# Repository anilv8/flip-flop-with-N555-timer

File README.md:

# Flip-Flop Circuit with N555 Timer
Double Sided PCB design of Flip-Flop circuitwith NE555 Timer using KiCad.
Dimensions: 25 mm x 27 mm.

# Schematic of circuit

### ERC Result:

# PCB Board
### Front Copper:

### Back Copper:

### Silkscreen:

## DRC Result:

## 3D view of PCB
### Front:

### Back:

# Gerber
### Front Copper:

### Back Copper:

# BOM
| Id  | Designator | Footprint | Quantity | Designation | Supplier and ref |
| --- | --- | --- | --- | --- | --- |
| 1   | R3  | R_Axial_DIN0204_L3.6mm_D1.6mm_P5.08mm_Horizontal | 1   | 100k |     |
| 2   | R4  | R_Axial_DIN0204_L3.6mm_D1.6mm_P5.08mm_Horizontal | 1   | 50k |     |
| 3   | D1,D2 | LED_D3.0mm | 2   | LED |     |
| 4   | U1  | DIP-8_W7.62mm_LongPads | 1   | NE555P |     |
| 5   | R2,R1 | R_Axial_DIN0204_L3.6mm_D1.6mm_P5.08mm_Horizontal | 2   | 330 |     |
| 6   | C2  | CP_Radial_D6.3mm_P2.50mm | 1   | 10u |     |
| 7   | C3  | C_Disc_D3.0mm_W1.6mm_P2.50mm | 1   | 0.1u |     |
| 8   | J2  | Molex_KK-254_AE-6410-02A_1x02\P2.54mm_Vertical | 1   | Conn\_01x02\_Pin |     |

# REFERENCES
[1]  https://www.udemy.com/course/kicad-ile-pcb-tasarimi-elektronik-kart-tasarimi/

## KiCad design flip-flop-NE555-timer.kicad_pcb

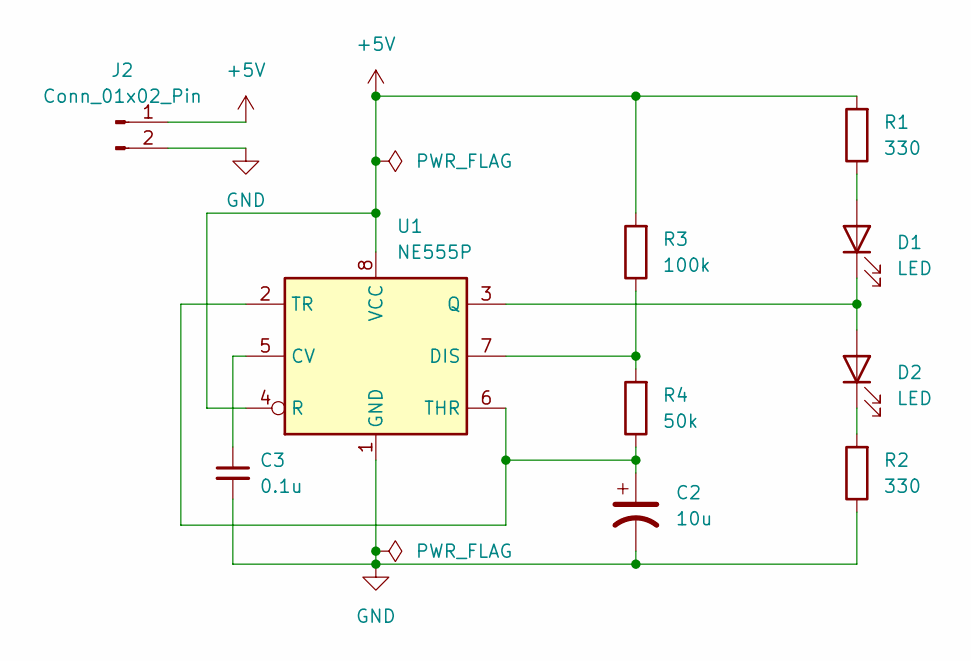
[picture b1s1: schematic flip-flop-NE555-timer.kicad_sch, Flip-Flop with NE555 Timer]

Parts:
C2: 10u; CP_Radial_D6.3mm_P2.50mm
C3: 0.1u; C_Disc_D3.0mm_W1.6mm_P2.50mm
D1, D2: LED; LED_D3.0mm
J2: Conn_01x02_Pin; Molex_KK-254_AE-6410-02A_1x02_P2.54mm_Vertical
R1, R2: 330; R_Axial_DIN0204_L3.6mm_D1.6mm_P5.08mm_Horizontal
R3: 100k; R_Axial_DIN0204_L3.6mm_D1.6mm_P5.08mm_Horizontal
R4: 50k; R_Axial_DIN0204_L3.6mm_D1.6mm_P5.08mm_Horizontal
U1: NE555P; DIP-8_W7.62mm_LongPads

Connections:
+5V: J2.1, R1.2, R3.2, U1.4 (R), U1.8 (VCC)
GND: C2.2, C3.2, J2.2, R2.1, U1.1 (GND)
unnamed: D1.2 (A), R1.1
unnamed: D1.1 (K), D2.2 (A), U1.3 (Q)
unnamed: D2.1 (K), R2.2
unnamed: C3.1, U1.5 (CV)
unnamed: R3.1, R4.2, U1.7 (DIS)
unnamed: C2.1, R4.1, U1.2 (TR), U1.6 (THR)

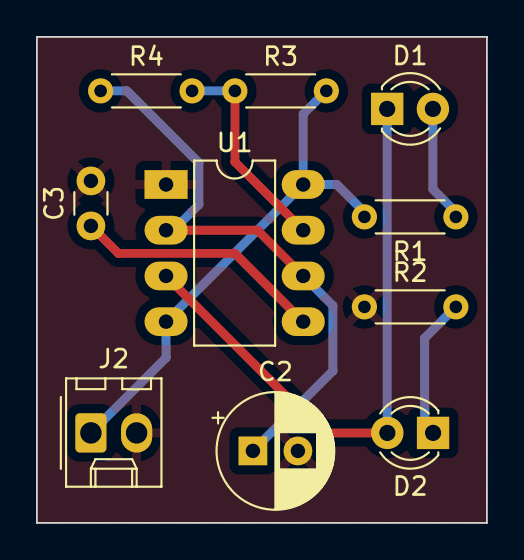
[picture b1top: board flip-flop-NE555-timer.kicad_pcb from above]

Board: 2 copper layers, 25.0 x 27.0 mm, 10 parts (0 on the bottom side), 8 nets.
